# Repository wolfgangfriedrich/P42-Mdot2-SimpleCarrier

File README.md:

A carrier to connect to a M.2 2230/3030 or 2242/3042 Board through USB, UART or I2C. All other signals are broken out to to TH testpoints.

List of features:

    M.2 slot with all pads on the board to accept any key slot M.2 module, if the correct connector is mounted.
    Specifically made for A key and E key, targeting WiFi, Bluetooth, WWAN adapter.
    Works with a subset of signals for B key and M key, but not as a USB memory interface for SSDs.
    All signals available on through hole test points on a 2.54mm (0.1") grid.
    PCIe signals are routed as differential pairs.
    USB-C set up for 5V 3A max power draw.
    Switching regulator to generate 3.3V 1.5A to power the M.2 module.
    1.8V LDO regulator to be able to work with the 1.8V UART and I2C signals.
    Power switch for the 3.3V to the M.2 module with an enable jumper and 500mA over-current protection.
    LEDs for 1.8V, 3.3V and switched 3.3V; LED for over-current condition.
    4 mounting holes.
    Mounting holes for nuts to secure 2230 or 2242 modules.
    Level shifter and connector to make UART accessible on a 3-pin header.
    Level shifter and QWIIC connector to make I2C accessible on a 3-pin header.
    Extra testpoints for GND, VBUS, 3.3V, 1.8V
    Design in KiCAD.

The design came to life initially to test my M.2 RP2350 board (https://www.tindie.com/products/pier42/pico2-m2). I needed a test platform to access all signals of the M.2 interface with E or A key. Single Board Computers with a M.2 port often don't access all pins, so I built this board and think it is very useful.

M.2 carrier boards are generally for B or M key SSDs to other internal interfaces. I am not aware of any breakout board for M.2 modules with enhanced functionality. There are a few passive breakout boards available that simply connect all pins to standard headers.

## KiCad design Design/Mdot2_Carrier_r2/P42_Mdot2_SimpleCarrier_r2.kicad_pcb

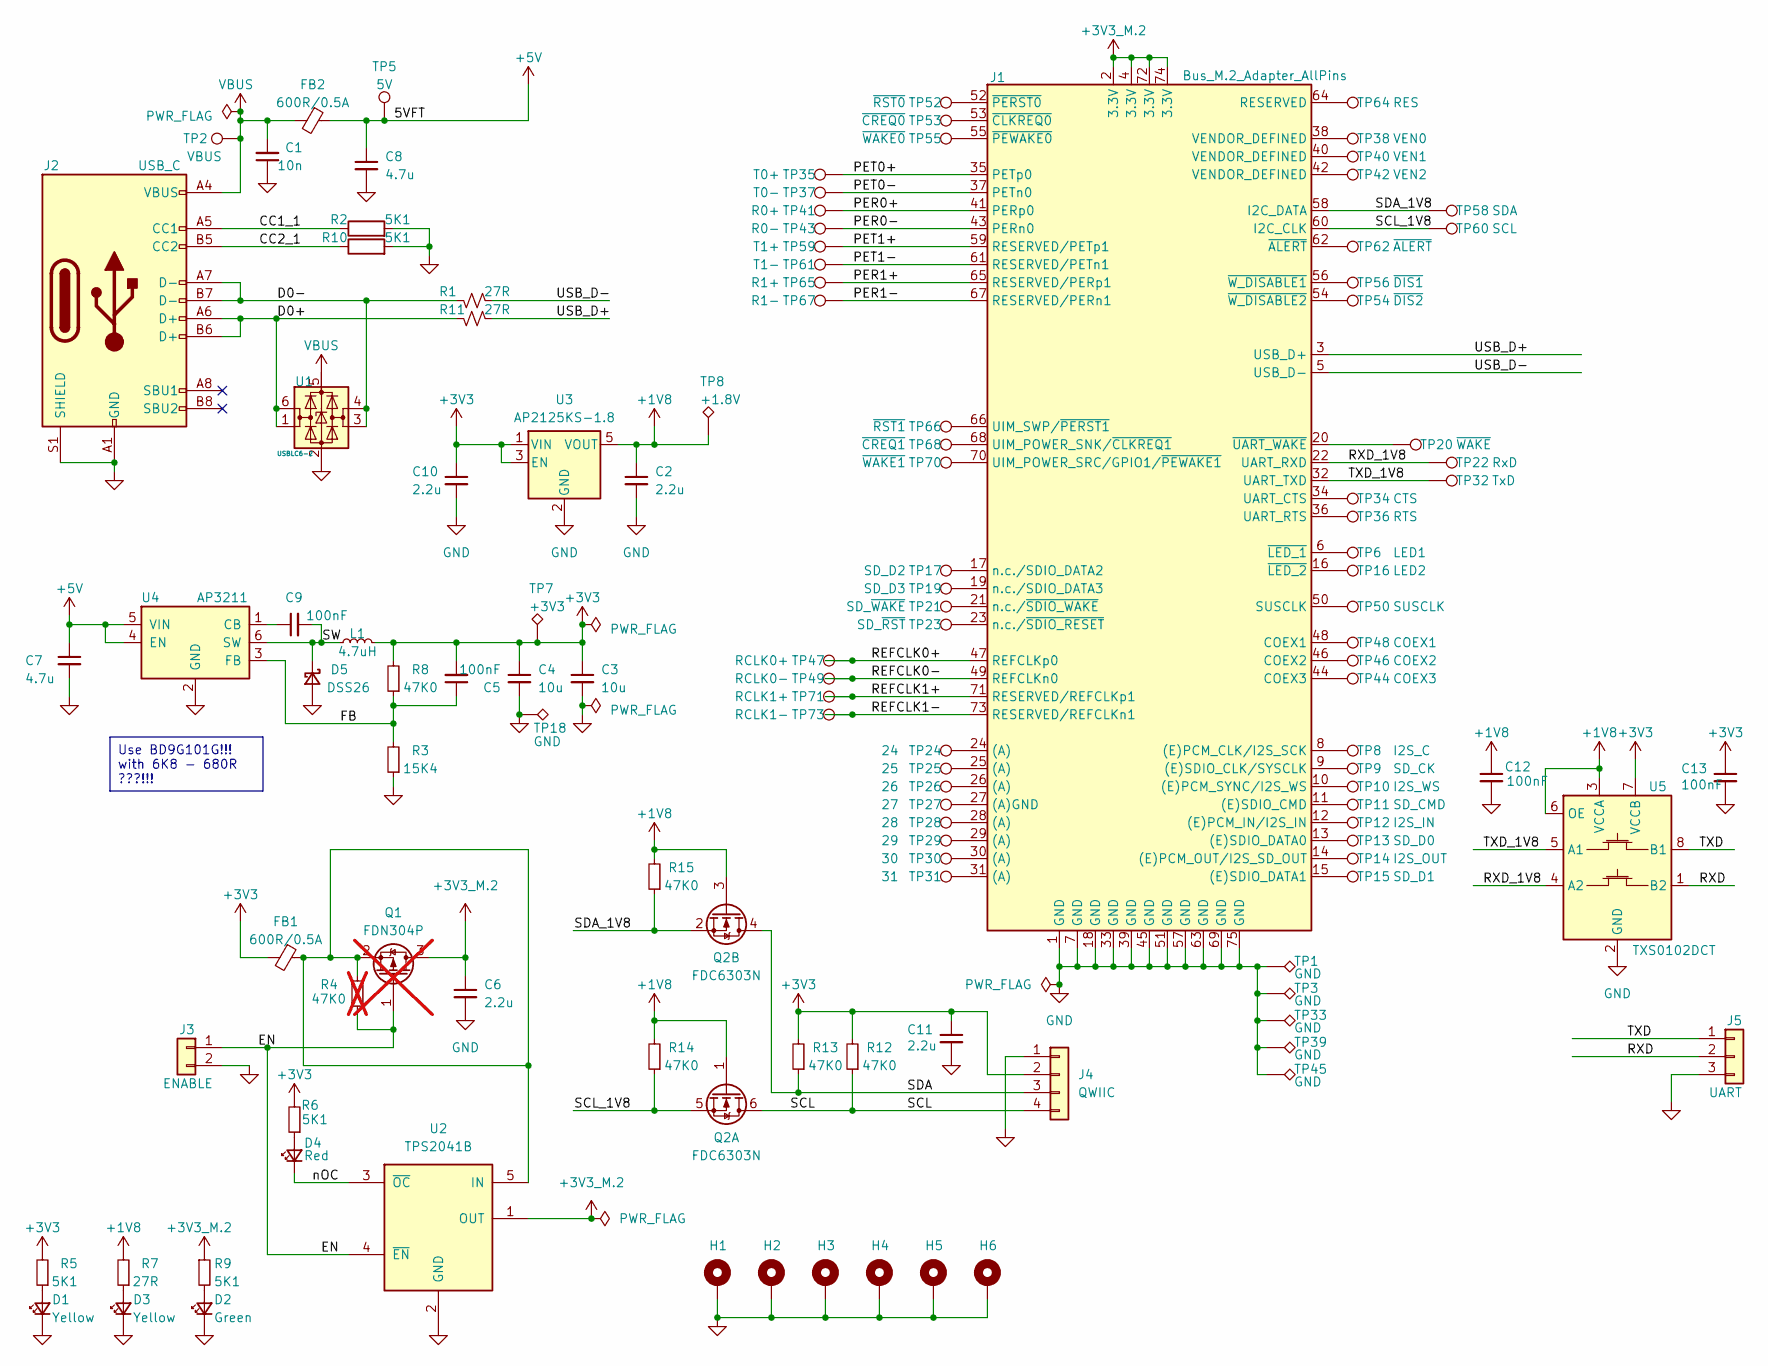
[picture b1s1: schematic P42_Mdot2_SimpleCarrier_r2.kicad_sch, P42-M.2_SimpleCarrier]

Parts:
C1: 10n; C_0603_1608Metric; Mfr PN na; JLCPCB # C57112
C2, C6, C10, C11: 2.2u; C_0603_1608Metric; Mfr PN na; JLCPCB # C23630
C3, C4: 10u; C_1206_3216Metric; Mfr PN CL31B106KBHNNNE; JLCPCB # C13585
C5, C12, C13: 100nF; C_0603_1608Metric; Mfr PN na; JLCPCB # C14663
C7, C8: 4.7u; C_0805_2012Metric; Mfr PN GRT21BR61H475KE13L; JLCPCB # C98192
C9: 100nF; C_0603_1608Metric; Mfr1 PN na; JLCPCB # C14663
D1, D3: Yellow; LED_0603_1608Metric; Mfr1 PN 150060YS75000; JLCPCB # C434424
D2: Green; LED_0603_1608Metric; Mfr1 PN 150060GS75000; JLCPCB # C434420
D4: Red; LED_0603_1608Metric; Mfr1 PN 150060RS75000; JLCPCB # C2286
D5: DSS26; D_SOD-123; Mfr PN SS26FL; JLCPCB # C511867
FB1, FB2: 600R/0.5A; L_0603_1608Metric; Mfr PN BLM18AG601SN1D; JLCPCB # C710380
H1, H2, H3, H4, H5, H6: MountingHole_Pad; MountingHole_3.2mm_M3_Pad_Via
J1: Bus_M.2_Adapter_AllPins; NGFF_M.2_AE-Key_AMP_MDT420; Mfr1 PN MDT420E01001; LCSC Part # C2761457
J2: USB_C; USB_C_Receptacle_G-Switch_GT-USB-7010ASV; Mfr PN GT-USB-7010ASV; LCSC Part # C2988369
J3: ENABLE; PinHeader_1x02_P2.54mm_Vertical; Mfr PN PH1-02-UA; JLCPCB # C492401
J4: QWIIC; JST_SH_SM04B-SRSS-TB_1x04-1MP_P1.00mm_Horizontal; Mfr1 PN SM04B-SRSS-TB(LF)(SN); JLCPCB # C160404
J5: UART; PinHeader_1x03_P2.54mm_Vertical; Mfr PN PH1-03-UA; JLCPCB # C49257
L1: 4.7uH; L_Bourns_SRN6045TA; Mfr2 PN VLS6045AF-6R8M; JLCPCB # C171792
Q1: FDN304P; SOT-23-3; Mfr1 PN FDN306P; LCSC Part # C154510; not fitted
Q2: FDC6303N; SOT-23-6; Mfr PN FDC6303N; JLCPCB # C5246389
R1, R7, R11: 27R; R_0603_1608Metric; Mfr PN na; JLCPCB # C25190
R2, R5, R6, R9, R10: 5K1; R_0603_1608Metric; Mfr PN na; JLCPCB # C23186
R3: 15K4; R_0603_1608Metric; Mfr PN na; JLCPCB # C2933150
R4: 47K0; R_0603_1608Metric; Mfr PN na; JLCPCB # C25819; not fitted
R8, R12, R13, R14, R15: 47K0; R_0603_1608Metric; Mfr PN na; JLCPCB # C25819
TP1, TP3, TP18, TP33, TP39, TP45: GND; THTPad_D1.5mm_Drill1.0mm
TP2: VBUS; THTPad_D1.5mm_Drill1.0mm
TP5: 5V; THTPad_D1.5mm_Drill1.0mm
TP6: LED1; THTPad_D1.5mm_Drill1.0mm
TP7: +3V3; THTPad_D1.5mm_Drill1.0mm
TP8: I2S_C; THTPad_D1.5mm_Drill1.0mm
TP9: SD_CK; THTPad_D1.5mm_Drill1.0mm
TP10: I2S_WS; THTPad_D1.5mm_Drill1.0mm
TP11: SD_CMD; THTPad_D1.5mm_Drill1.0mm
TP12: I2S_IN; THTPad_D1.5mm_Drill1.0mm
TP13: SD_D0; THTPad_D1.5mm_Drill1.0mm
TP14: I2S_OUT; THTPad_D1.5mm_Drill1.0mm
TP15: SD_D1; THTPad_D1.5mm_Drill1.0mm
TP16: LED2; THTPad_D1.5mm_Drill1.0mm
TP17: SD_D2; THTPad_D1.5mm_Drill1.0mm
TP19: SD_D3; THTPad_D1.5mm_Drill1.0mm
TP20: ~{WAKE}; THTPad_D1.5mm_Drill1.0mm
TP21: SD_~{WAKE}; THTPad_D1.5mm_Drill1.0mm
TP22: RxD; THTPad_D1.5mm_Drill1.0mm
TP23: SD_~{RST}; THTPad_D1.5mm_Drill1.0mm
TP24: 24; THTPad_D1.5mm_Drill1.0mm
TP25: 25; THTPad_D1.5mm_Drill1.0mm
TP26: 26; THTPad_D1.5mm_Drill1.0mm
TP27: 27; THTPad_D1.5mm_Drill1.0mm
TP28: 28; THTPad_D1.5mm_Drill1.0mm
TP29: 29; THTPad_D1.5mm_Drill1.0mm
TP30: 30; THTPad_D1.5mm_Drill1.0mm
TP31: 31; THTPad_D1.5mm_Drill1.0mm
TP32: TxD; THTPad_D1.5mm_Drill1.0mm
TP34: CTS; THTPad_D1.5mm_Drill1.0mm
TP35: T0+; THTPad_D1.5mm_Drill1.0mm
TP36: RTS; THTPad_D1.5mm_Drill1.0mm
TP37: T0-; THTPad_D1.5mm_Drill1.0mm
TP38: VEN0; THTPad_D1.5mm_Drill1.0mm
TP40: VEN1; THTPad_D1.5mm_Drill1.0mm
TP41: R0+; THTPad_D1.5mm_Drill1.0mm
TP42: VEN2; THTPad_D1.5mm_Drill1.0mm
TP43: R0-; THTPad_D1.5mm_Drill1.0mm
TP44: COEX3; THTPad_D1.5mm_Drill1.0mm
TP46: COEX2; THTPad_D1.5mm_Drill1.0mm
TP47: RCLK0+; THTPad_D1.5mm_Drill1.0mm
TP48: COEX1; THTPad_D1.5mm_Drill1.0mm
TP49: RCLK0-; THTPad_D1.5mm_Drill1.0mm
TP50: SUSCLK; THTPad_D1.5mm_Drill1.0mm
TP52: ~{RST0}; THTPad_D1.5mm_Drill1.0mm
TP53: ~{CREQ0}; THTPad_D1.5mm_Drill1.0mm
TP54: ~{DIS2}; THTPad_D1.5mm_Drill1.0mm
TP55: ~{WAKE0}; THTPad_D1.5mm_Drill1.0mm
TP56: ~{DIS1}; THTPad_D1.5mm_Drill1.0mm
TP58: SDA; THTPad_D1.5mm_Drill1.0mm
TP59: T1+; THTPad_D1.5mm_Drill1.0mm
TP60: SCL; THTPad_D1.5mm_Drill1.0mm
TP61: T1-; THTPad_D1.5mm_Drill1.0mm
TP62: ~{ALERT}; THTPad_D1.5mm_Drill1.0mm
TP64: RES; THTPad_D1.5mm_Drill1.0mm
TP65: R1+; THTPad_D1.5mm_Drill1.0mm
TP66: ~{RST1}; THTPad_D1.5mm_Drill1.0mm
TP67: R1-; THTPad_D1.5mm_Drill1.0mm
TP68: ~{CREQ1}; THTPad_D1.5mm_Drill1.0mm
TP70: ~{WAKE1}; THTPad_D1.5mm_Drill1.0mm
TP71: RCLK1+; THTPad_D1.5mm_Drill1.0mm
TP73: RCLK1-; THTPad_D1.5mm_Drill1.0mm
U1: USBLC6-2; SOT-666; Mfr PN USBLC6-2P6; JLCPCB # C2827693
U2: TPS2041B; SOT-23-5; Mfr PN TPS2041BDBVR; JLCPCB # C51386
U3: AP2125KS-1.8; SOT-23-5; Mfr PN AP2125KS-1.8TRG1; JLCPCB # C7214645
U4: AP3211; SOT-23-6; Mfr3 PN AP64060WU-7 (6.8uH, 69.8K, 22.1K); JLCPCB # C154863
U5: TXS0102DCT; SSOP-8_2.95x2.8mm_P0.65mm; Mfr PN TXS0102DCTR; JLCPCB # C324082

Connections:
+3V3: C3.1, C4.1, C5.2, C10.1, C11.1, C13.1, FB1.2, J4.2, L1.2, R5.2, R6.2, R8.2, R12.2, R13.2, TP7.1, U3.1 (VIN), U3.3 (EN), U5.7 (VCCB)
+3V3_M.2: C6.1, J1.2 (3.3V), J1.4 (3.3V), J1.72 (3.3V), J1.74 (3.3V), Q1.3 (D), R9.1, U2.1 (OUT)
+5V: C7.1, C8.1, FB2.1, TP5.1, U4.4 (EN), U4.5 (VIN)
/CC1_1: J2.A5 (CC1), R2.1
/CC2_1: J2.B5 (CC2), R10.1
/D0+: J2.A6 (D+), J2.B6 (D+), R11.2, U1.1 (I/O1), U1.6 (I/O1)
/D0-: J2.A7 (D-), J2.B7 (D-), R1.2, U1.3 (I/O2), U1.4 (I/O2)
/EN: J3.1, Q1.1 (G), R4.1, U2.4 (~EN)
/FB: C5.1, R3.2, R8.1, U4.3 (FB)
/PER0+: J1.41 (PERp0), TP41.1
/PER0-: J1.43 (PERn0), TP43.1
/PER1+: J1.65 (RESERVED/PERp1), TP65.1
/PER1-: J1.67 (RESERVED/PERn1), TP67.1
/PET0+: J1.35 (PETp0), TP35.1
/PET0-: J1.37 (PETn0), TP37.1
/PET1+: J1.59 (RESERVED/PETp1), TP59.1
/PET1-: J1.61 (RESERVED/PETn1), TP61.1
/REFCLK0+: J1.47 (REFCLKp0), TP47.1
/REFCLK0-: J1.49 (REFCLKn0), TP49.1
/REFCLK1+: J1.71 (RESERVED/REFCLKp1), TP71.1
/REFCLK1-: J1.73 (RESERVED/REFCLKn1), TP73.1
/RXD: J5.2, U5.1 (B2)
/RXD_1V8: J1.22 (UART_RXD), TP22.1, U5.4 (A2)
/SCL: J4.4, Q2.6 (D), R12.1
/SCL_1V8: J1.60 (I2C_CLK), Q2.5 (S), R14.1, TP60.1
/SDA: J4.3, Q2.4 (D), R13.1
/SDA_1V8: J1.58 (I2C_DATA), Q2.2 (S), R15.1, TP58.1
/SW: C9.2, D5.1 (K), L1.1, U4.6 (SW)
/TXD: J5.1, U5.8 (B1)
/TXD_1V8: J1.32 (UART_TXD), TP32.1, U5.5 (A1)
/USB_D+: J1.3 (USB_D+), R11.1
/USB_D-: J1.5 (USB_D-), R1.1
/nOC: D4.1 (K), U2.3 (~OC)
GND: C1.1, C2.2, C3.2, C4.2, C6.2, C7.2, C8.2, C10.2, C11.2, C12.2, C13.2, D1.1 (K), D2.1 (K), D3.1 (K), D5.2 (A), H1.1, H2.1, H3.1, H4.1, H5.1, H6.1, J1.1 (GND), J1.7 (GND), J1.18 (GND), J1.33 (GND), J1.39 (GND), J1.45 (GND), J1.51 (GND), J1.57 (GND), J1.63 (GND), J1.69 (GND), J1.75 (GND), J2.A1 (GND), J2.A12 (GND), J2.B1 (GND), J2.B12 (GND), J2.S1 (SHIELD), J3.2, J4.1, J5.3, R2.2, R3.1, R10.2, TP1.1, TP3.1, TP18.1, TP33.1, TP39.1, TP45.1, U1.2 (GND), U2.2 (GND), U3.2 (GND), U4.2 (GND), U5.2 (GND)
unnamed: D1.2 (A), R5.1
unnamed: D2.2 (A), R9.2
unnamed: D3.2 (A), R7.1
unnamed: D4.2 (A), R6.1
unnamed: J1.24 ((A)), TP24.1
unnamed: J1.25 ((A)), TP25.1
unnamed: J1.26 ((A)), TP26.1
unnamed: J1.28 ((A)), TP28.1
unnamed: J1.29 ((A)), TP29.1
unnamed: J1.30 ((A)), TP30.1
unnamed: J1.31 ((A)), TP31.1
unnamed: J1.27 ((A)GND), TP27.1
unnamed: J1.12 ((E)PCM_IN/I2S_IN), TP12.1
unnamed: J1.14 ((E)PCM_OUT/I2S_SD_OUT), TP14.1
unnamed: J1.10 ((E)PCM_SYNC/I2S_WS), TP10.1
unnamed: J1.9 ((E)SDIO_CLK/SYSCLK), TP9.1
unnamed: J1.11 ((E)SDIO_CMD), TP11.1
unnamed: J1.13 ((E)SDIO_DATA0), TP13.1
unnamed: J1.15 ((E)SDIO_DATA1), TP15.1
unnamed: J1.48 (COEX1), TP48.1
unnamed: J1.46 (COEX2), TP46.1
unnamed: J1.44 (COEX3), TP44.1
unnamed: J1.64 (RESERVED), TP64.1
unnamed: J1.50 (SUSCLK), TP50.1
unnamed: J1.34 (UART_CTS), TP34.1
unnamed: J1.36 (UART_RTS), TP36.1
unnamed: J1.68 (UIM_POWER_SNK/~CLKREQ1), TP68.1
unnamed: J1.70 (UIM_POWER_SRC/GPIO1/~PEWAKE1), TP70.1
unnamed: J1.66 (UIM_SWP/~PERST1), TP66.1
unnamed: J1.38 (VENDOR_DEFINED), TP38.1
unnamed: J1.40 (VENDOR_DEFINED), TP40.1
unnamed: J1.42 (VENDOR_DEFINED), TP42.1
unnamed: J1.17 (n.c./SDIO_DATA2), TP17.1
unnamed: J1.19 (n.c./SDIO_DATA3), TP19.1
unnamed: J1.23 (n.c./~SDIO_RESET), TP23.1
unnamed: J1.21 (n.c./~SDIO_WAKE), TP21.1
unnamed: J1.62 (~ALERT), TP62.1
unnamed: J1.53 (~CLKREQ0), TP53.1
unnamed: J1.6 (~LED_1), TP6.1
unnamed: J1.16 (~LED_2), TP16.1
unnamed: J1.52 (~PERST0), TP52.1
unnamed: J1.55 (~PEWAKE0), TP55.1
unnamed: J1.20 (~UART_WAKE), TP20.1
unnamed: J1.56 (~W_DISABLE1), TP56.1
unnamed: J1.54 (~W_DISABLE2), TP54.1
unnamed: FB1.1, Q1.2 (S), R4.2, U2.5 (IN)
unnamed: C9.1, U4.1 (CB)
VBUS: C1.2, FB2.2, J2.A4 (VBUS), J2.A9 (VBUS), J2.B4 (VBUS), J2.B9 (VBUS), TP2.1, U1.5 (VBUS)

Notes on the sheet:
Use BD9G101G!!! with 6K8 - 680R ???!!!

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
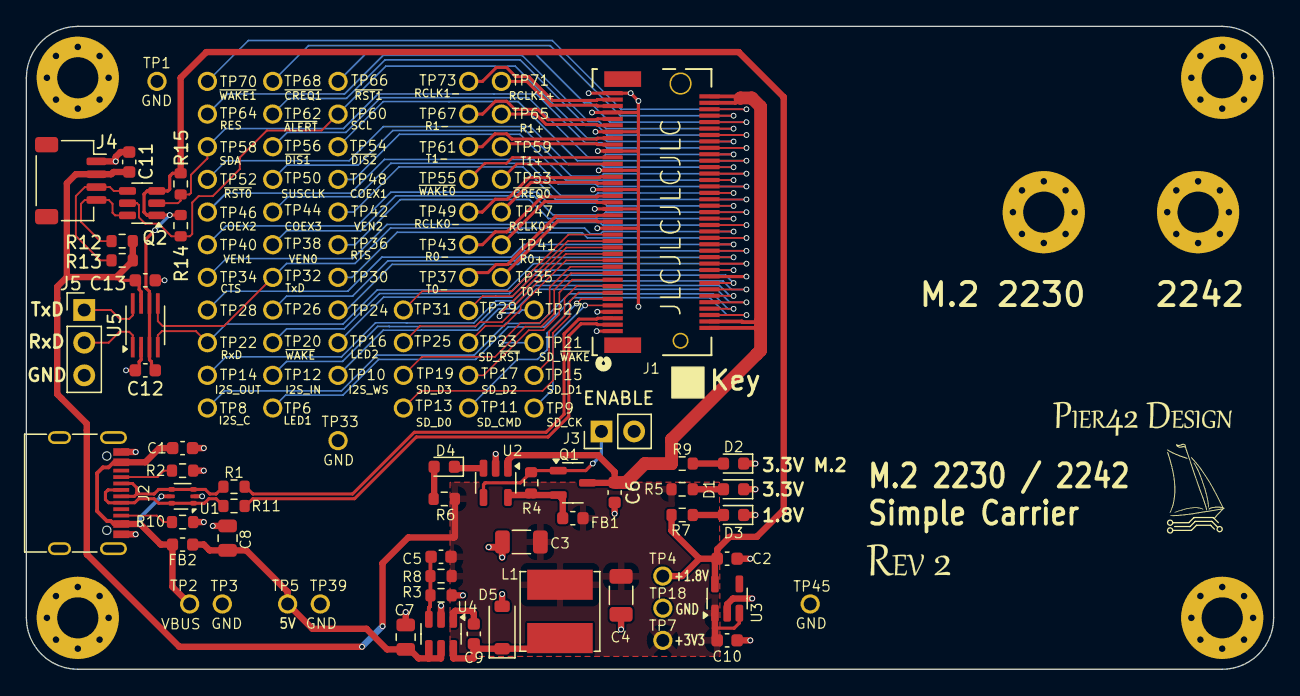
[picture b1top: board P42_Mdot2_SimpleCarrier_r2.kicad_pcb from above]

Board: 2 copper layers, 97.0 x 50.0 mm, 122 parts (0 on the bottom side), 84 nets.

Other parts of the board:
TP4: +1.8V; THTPad_D1.5mm_Drill1.0mm

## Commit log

2025-07-13 Initial upload
    Initial design files
2025-07-13 Create README.md
    read it.
2025-07-13 Update README.md
    read it again.
2025-07-13 Create BOM_Simple-M.2-Adapter_rev2.pdf
    Added BOM pdf

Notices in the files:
Design/Mdot2_Carrier_r2/P42_Mdot2_SimpleCarrier_r2.kicad_pcb:
(c) 2025 Wolfgang Friedrich
Creative Commons Attribution-ShareAlike 4.0 International (CC BY-SA 4.0)
